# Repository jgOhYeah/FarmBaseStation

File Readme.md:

# Base station for connecting remote sensors to Thingsboard.
Remote sensors use [PJON over LoRa](https://github.com/gioblu/PJON) radio to communicate.
The [Thingsboard Gateway MQTT API](https://thingsboard.io/docs/reference/gateway-mqtt-api/) is used to connect on the Thingsboard side.

See [here](https://github.com/jgOhYeah/Farm-PJON-LoRa-network) for other sensors and more information on the system.

Written by Jotham Gates
August 2023

## Photos
<!-- 
 -->

## Getting started
The Github repository containing all design files and code is [here](https://github.com/jgOhYeah/FarmBaseStation).

1. Install Platform IO.
2. Open the project in the [`BaseStationCode`](./BaseStationCode/) directory.
3. Create a copy of [`BaseStationCode/credentials.example.ini`](./BaseStationCode/credentials.example.ini) and name this `credentials.ini`. Fill out the settings in this file for the WiFi network to connect to, MQTT broker, Thingsboard credentials and Over The Air (OTA) update settings.
4. Upload the code to the ESP32.
5. Assemble the electronics as shown in the schematics and optionally place inside a case.
6. Test with other sensors and the Thingsboard server.

## Updating using OTA updates
Over the air (OTA) updates can be used to update the software on the base station once it has been programmed for the first time. To do this:
1. Edit the upload port and auth flags in `credentials.ini` to match those currently set on the device.
2. Change the active Platform IO environment to `Tardis-OTA` from its default `Tardis` environment (likewise for the `TVAnt` environemnt for ethernet).
3. Compile and upload code as normal.

## Schematics
The base station uses an ESP32 development board as its base. An SX1278 LoRa radio module breakout board is connected via jumper leads. LEDs are soldered along with their respective current limiting resistors to wires that can be plugged into the ESP32 board. An audio amplifier and speaker can also be connected for alarm functionality. I salvaged this from the sound effects module of a broken children's ride on toy car.

## Fun part / experiments
I originally planned to use the build in DAC of the ESP32 to play sounds on alarm conditions. At this point I haven't succeded in this (currently using the [TunePlayer](https://github.com/jgOhYeah/TunePlayer) library to play simple monotonic songs instead). I did come across the [ESP32-A2DP](https://github.com/pschatzmann/ESP32-A2DP) library that allows the use of this unit as a terrible sounding bluetooth speaker.

[This sketch](Fun/BluetoothSpeaker/BluetoothSpeaker.ino) is the `bt_music_receiver_to_internal_dac` example from the ESP32-A2DP library with the addition of flashing lights.

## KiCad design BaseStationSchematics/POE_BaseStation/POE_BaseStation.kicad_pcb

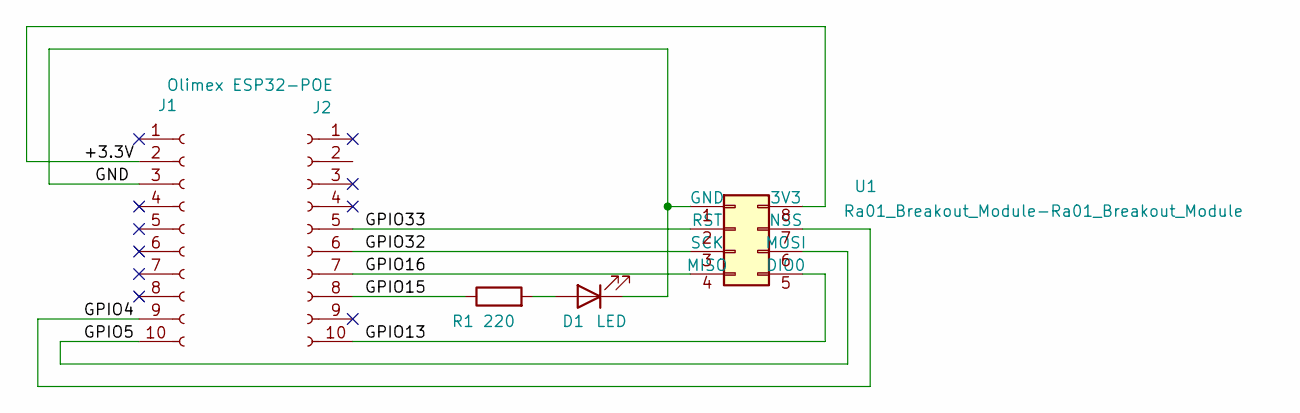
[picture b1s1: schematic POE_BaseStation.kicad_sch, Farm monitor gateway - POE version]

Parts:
D1: LED; LED_D3.0mm
J1: Olimex ESP32-POE; PinSocket_1x10_P2.54mm_Vertical
J2: Conn_01x10_Socket; PinSocket_1x10_P2.54mm_Vertical
R1: 220; R_Axial_DIN0207_L6.3mm_D2.5mm_P15.24mm_Horizontal
U1: Ra01_Breakout_Module-Ra01_Breakout_Module; DIP-8_W7.62mm_Socket_LongPads

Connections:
/+3.3V: J1.2, U1.8 (3V3)
/GND: D1.1 (K), J1.3, U1.1 (GND)
/GPIO4: J1.9, U1.7 (NSS)
/GPIO5: J1.10, U1.6 (MOSI)
/GPIO13: J2.10, U1.5 (DIO0)
/GPIO15: J2.8, R1.1
/GPIO16: J2.7, U1.4 (MISO)
/GPIO32: J2.6, U1.3 (SCK)
/GPIO33: J2.5, U1.2 (RST)
unnamed: D1.2 (A), R1.2

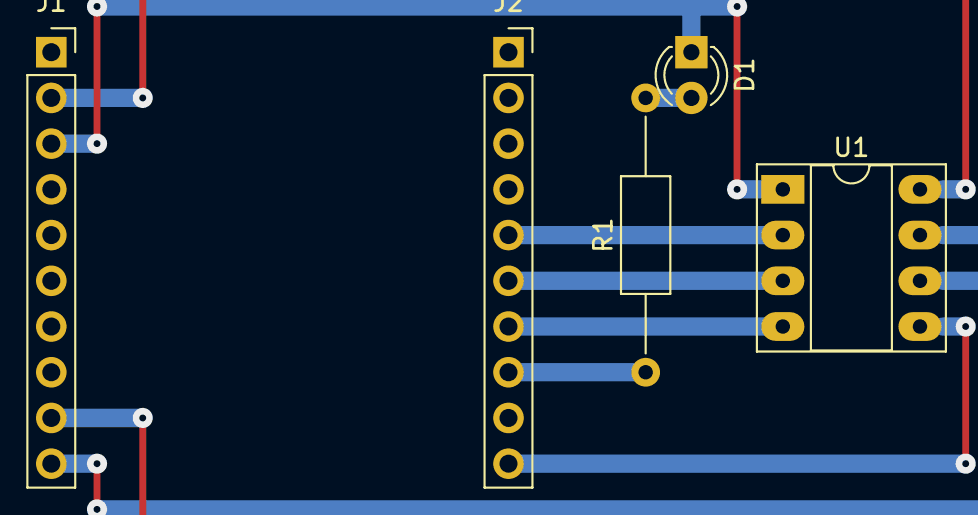
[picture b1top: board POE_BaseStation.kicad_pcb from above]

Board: 2 copper layers, 5 parts (0 on the bottom side), 10 nets.

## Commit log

2023-08-08 Added networking structure
2023-08-08 Added fields manager
2023-08-09 Added topics and started device manager
2023-08-09 Moved devices and fields to separate files
2023-08-10 Converted to use cpp files
2023-08-10 Added all current fields
2023-08-10 Started decoding packets
2023-08-10 Added readme and fixed doxyfile
2023-08-11 Added decoding of payloads to a device
2023-08-12 Added decoding packets and publishing mqtt Need to fix template linking errors
2023-08-12 Compiles now
2023-08-12 Added fake data as its own task, fixed field conversions
2023-08-12 Can successfully decode fake packets and send to thingsboard
2023-08-12 Added snr and rssi to packets, mostly written radio hardware code
2023-08-13 Successfully responds to rpc calls for me
2023-08-14 Connected alarms to rpc queue, started schematic
2023-08-14 Schematic mostly created, added LoRa watchdog task
2023-08-14 Started adding rpc packet encoding
2023-08-15 Rpc calls mostly written, needs further debugging
2023-08-16 Added github pages doxygen action
2023-08-16 Adding audio, doesn't work when defined / included
2023-08-18 Got tune player working
2023-08-18 Deploying to gh-pages from @ jgOhYeah/FarmBaseStation@23fb38ca431f9e87944fd8c27143e8e98b18d628 🚀
2023-08-18 Initial gh-pages commit
2023-08-18 Removng unecessary debugging information, added bluetooth speaker example.
2023-08-19 Replaced tune with improved one, updated water baby address
2023-08-19 Deploying to gh-pages from @ jgOhYeah/FarmBaseStation@0b4f70a7d4a7e1683401a2061ada4643715b7b26 🚀
2023-08-25 Added images and improved readme
2023-08-25 Added readme to doxygen
2023-08-25 Deploying to gh-pages from @ jgOhYeah/FarmBaseStation@1a84b020fb26933da942515ff9683b9f3f939816 🚀
2023-10-05 Added images, ino file and link to doxygen
2023-10-05 Deploying to gh-pages from @ jgOhYeah/FarmBaseStation@c969e54fe996c88d1b3c2a26c3f4b9cdd3699aa9 🚀
2023-11-02 Added a queue between pjon receive and mqtt, added status attributes
2023-11-02 Deploying to gh-pages from @ jgOhYeah/FarmBaseStation@2ad6d0c07d5802e4b04efd281d6e84f133e2ff78 🚀
2023-11-03 Tidying up, added reset rpc, leds flash as status lights, audio stops on alarm stop.
2023-11-03 Deploying to gh-pages from @ jgOhYeah/FarmBaseStation@7977273d1b6a4a59a75dd68052357b5af0aa7e7f 🚀
2023-11-05 TX required detection behaves as expected.
2023-11-05 Deploying to gh-pages from @ jgOhYeah/FarmBaseStation@636a997f74f692da4177f6e754ec8dcf996e3eba 🚀
2023-11-05 LEDs are driven by their own task
2023-11-05 Deploying to gh-pages from @ jgOhYeah/FarmBaseStation@bb926971d034e67fde1da12f53ebaad16417cc12 🚀
2024-01-05 Wifi connection process is restarted if the unit cannot connect for 60s
2024-01-05 Deploying to gh-pages from @ jgOhYeah/FarmBaseStation@c2397a1c3846f81a618b0c5bbeb3ac0cacc69014 🚀
2024-01-14 Added OTA update capability and fixed compile warnings in rpc.cpp and audio.cpp
2024-01-14 Deploying to gh-pages from @ jgOhYeah/FarmBaseStation@923d1fc1b9dbba0c3ae48aba4c72a23c220fe6cc 🚀
2024-01-27 Added temperature and humidity to pump monitor
2024-01-27 Deploying to gh-pages from @ jgOhYeah/FarmBaseStation@1935daa38fc3e34f44f8f8ab9e909fa3c12cbe40 🚀
2024-06-26 Proposed fix for incorrect temperature signs between 0 and -1 degree
2024-06-26 Deploying to gh-pages from @ jgOhYeah/FarmBaseStation@b1d4c57955fd0795b754babdf795183075a2dcec 🚀
2024-06-29 Updating version and dates
2024-06-29 Deploying to gh-pages from @ jgOhYeah/FarmBaseStation@f84ab17afecf2f3527e210573d0510aa3088031a 🚀
2024-07-03 Increased MQTT queue size to cope better with server outages.
2024-07-03 Deploying to gh-pages from @ jgOhYeah/FarmBaseStation@85357da2ad194dcbc300ff12b77bc1e841846edb 🚀
2024-09-24 Plotting ADC max and min in plot strain gauge, basic raw compensation in plotter.
2024-12-18 Fixed SW_VERSION typo, added electric fence monitor field and device
2024-12-18 Deploying to gh-pages from @ jgOhYeah/FarmBaseStation@8355eea0d61ade21f1b2034f5a938f962035ca94 🚀
2024-12-20 Swapped to platform IO
2024-12-20 Updated doxygen for new folders
2024-12-20 Deploying to gh-pages from @ jgOhYeah/FarmBaseStation@8fe6d848f2b62b4e2f91603648c2725e88d7c350 🚀
2024-12-24 Adding board config to platform.ini, incorrect POE schematic added
2024-12-24 Deploying to gh-pages from @ jgOhYeah/FarmBaseStation@2c60199809be77c1e2538e07e14546e28c36e219 🚀
2024-12-24 Made speaker and external LEDs optional, pins defined in platformio.ini
2024-12-24 Deploying to gh-pages from @ jgOhYeah/FarmBaseStation@21131a57327696d5a918ab77e07bf194de66fbe0 🚀
2024-12-26 Schematic and board layout matches POE, started adding ethernet support
2024-12-28 TVAnt uses tasmota platform, compiles with ethernet
2024-12-28 Deploying to gh-pages from @ jgOhYeah/FarmBaseStation@2ca0b70c1cf6be140ad69c22965882b7784ff40d 🚀
2024-12-28 Moved all credentials to build, updated json documents, added version attribute upload
2024-12-28 Deploying to gh-pages from @ jgOhYeah/FarmBaseStation@31ec8ab4abcf1d5e50cf23c305c3d83d3d69b955 🚀
2024-12-28 Fixed logging messages not showing
2024-12-28 Deploying to gh-pages from @ jgOhYeah/FarmBaseStation@a61eff38b8dd830441598f3c4880131b9194630c 🚀
2024-12-30 Added temperature to fence monitor, hopefully fixed attribute on reconnect blocking, flashes LEDs whilst updating.
2024-12-30 Deploying to gh-pages from @ jgOhYeah/FarmBaseStation@6a971113b869e679b23d35051b047d8cb0ba4d2c 🚀
2024-12-31 Added actually decode method to fields, simplified slightly.
2024-12-31 PJON Acknowledgement works when requested
2025-01-03 Added acknowledge delay
2025-01-03 Deploying to gh-pages from @ jgOhYeah/FarmBaseStation@d9111d8092b2d6b1a4f55f5558cf6b81a4f3a303 🚀
2025-01-04 Added doorbell sound
2025-01-04 Deploying to gh-pages from @ jgOhYeah/FarmBaseStation@ea41023a8d742157001bc689b04eae82c3a88713 🚀
2025-01-04 Added barometer and local timeseries
2025-01-04 Deploying to gh-pages from @ jgOhYeah/FarmBaseStation@76f5878e64f92529503690d459148972de33eb4c 🚀
2025-01-25 Added air conditioner base files
2025-01-26 Started to implement air conditioner IR, printing reset reason and time to attribute.
2025-01-26 Deploying to gh-pages from @ jgOhYeah/FarmBaseStation@10db8877dad01c100f8e19e44013f68f9d078a6f 🚀
2025-01-27 Added air conditioner attributes
2025-01-27 Deploying to gh-pages from @ jgOhYeah/FarmBaseStation@33f98c04ca5712dfc8a322ffd3bd65b6d868ef2a 🚀
